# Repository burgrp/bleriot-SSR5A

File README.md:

# BleRiot SSR5A

SSR5A is a mains-powered five-channel BleRiot switch intended primarily for
zone thermo-electric actuators in hydronic heating systems. Each independently
controlled output switches mains line through a zero-cross optotriac and triac.

The board combines a PY32F030 microcontroller, PAN2110 radio, five output
channels, a WS2812B status LED, and an isolated 3.3 V mains power supply. The
outputs are on/off switches; they are not phase-angle dimmers.

## Connections

Connector numbering follows the KiCad schematic.

| Connector | Pin 1 | Pin 2 | Pin 3 |
| --- | --- | --- | --- |
| `IN1` | Line (L) | Neutral (N) | Protective earth (PE) |
| `J1` | Channel 1 switched line | Neutral | Protective earth |
| `J2` | Channel 2 switched line | Neutral | Protective earth |
| `J3` | Channel 3 switched line | Neutral | Protective earth |
| `J4` | Channel 4 switched line | Neutral | Protective earth |
| `J5` | Channel 5 switched line | Neutral | Protective earth |

Each channel uses a MOC306x zero-cross optotriac and BTA08S-600CW triac. Its
on-board indicator LED follows the output directly.

## BleRiot Registers

An enabled channel is exposed as a writable boolean register:

| Tag | Register |
| ---: | --- |
| 1 | `ssr.channel.1` |
| 2 | `ssr.channel.2` |
| 3 | `ssr.channel.3` |
| 4 | `ssr.channel.4` |
| 5 | `ssr.channel.5` |

Each channel has inventory-as-code configuration in
[`fw/cmd/dev/main.go`](fw/cmd/dev/main.go):

- `Disabled` omits the register and holds the physical output off.
- `Inverted` reverses the logical-to-physical output mapping.
- `Default` selects the logical value applied after power-on and RF link loss.

Disabled takes precedence over inversion and the default. At startup, firmware
first biases every active-low triac control inactive, then applies the configured
defaults.

The node considers the BleRiot link offline after five seconds without a valid
packet. On the online-to-offline transition, it immediately restores every
channel to its configured logical `Default` and reapplies the corresponding
physical output level. This fail-safe also honors `Inverted`; for example, an
inverted channel with `Default: false` is physically energized while offline.
Choose defaults for the required safe state of the installation.

The smart LED on `PA6` shows the link and logical channel state. While online it
uses the idle color when every enabled channel register is false and the active
color when at least one is true, regardless of output inversion. It blinks red
while the link is offline.

The RF-loss behavior has been verified on hardware: channel 1 was commanded on,
the hub was stopped, and its active-low MCU output returned inactive after the
five-second link timeout. After reconnecting, all five registers reported their
configured false defaults.

## Hardware And Firmware

| Function | MCU pin |
| --- | --- |
| Channel 1 | `PA11` |
| Channel 2 | `PA12` |
| Channel 3 | `PA15` |
| Channel 4 | `PB3` |
| Channel 5 | `PB4` |
| WS2812B data | `PA6` |
| PAN2110 CSN | `PA4` |
| PAN2110 SCK | `PA5` |
| PAN2110 data | `PA7` |

The importable `ssr5a` firmware exports `Run` and targets the `py32f030x8`
profile. Its device type owns the scheduler-none build policy and 100 kHz
attach-mode pyOCD settings. The local inventory bridges the radio node to a
Registry server. The SWD connector carries SWDIO, ground, and SWCLK but no reset
or target-voltage connection.

## Repository Layout

- [`board/`](board/) contains the KiCad schematic, PCB, BOM, and fabrication
  outputs.
- [`fw/`](fw/) contains the importable TinyGo firmware, tests, and build profile.
- [`fw/spec/`](fw/spec/) contains configuration, the config-dependent register
  table, chip, and firmware manifest.
- [`fw/cmd/dev/`](fw/cmd/dev/) contains the local inventory and BleRiot CLI.
- [`fw-orig/`](fw-orig/) contains the original MicroPython firmware for reference.
- [`sub/hw-kicad/`](sub/hw-kicad/) is the shared KiCad library submodule.

Initialize the shared hardware library after cloning:

```sh
git submodule update --init --recursive
```

## Build And Test

The firmware requires Go, TinyGo with Puya target support, GNU Arm Embedded
binutils, and pyOCD with the Puya CMSIS pack.

```sh
go -C fw test ./...
go -C fw run ./cmd/dev node gen --name ssr
go -C fw run ./cmd/dev node build --name ssr --disassembly
go -C fw run ./cmd/dev node build --name ssr --flash --rtt
```

With a Registry server running, start the local hub:

```sh
go -C fw run ./cmd/dev hub --registry http://localhost:8080 --diagnostics rf
```

## Safety

This design connects directly to hazardous mains voltage. Assembly,
installation, testing, and enclosure work must be performed by suitably
qualified people using applicable electrical codes and safe isolation
practices. Independently verify protection, creepage and clearance, protective
earth continuity, enclosure construction, triac thermal limits, and actuator
ratings before deployment.

Do not wire mains or an actuator from this README alone. Verify the assembled
board against the schematic, PCB, and actuator manufacturer's documentation.

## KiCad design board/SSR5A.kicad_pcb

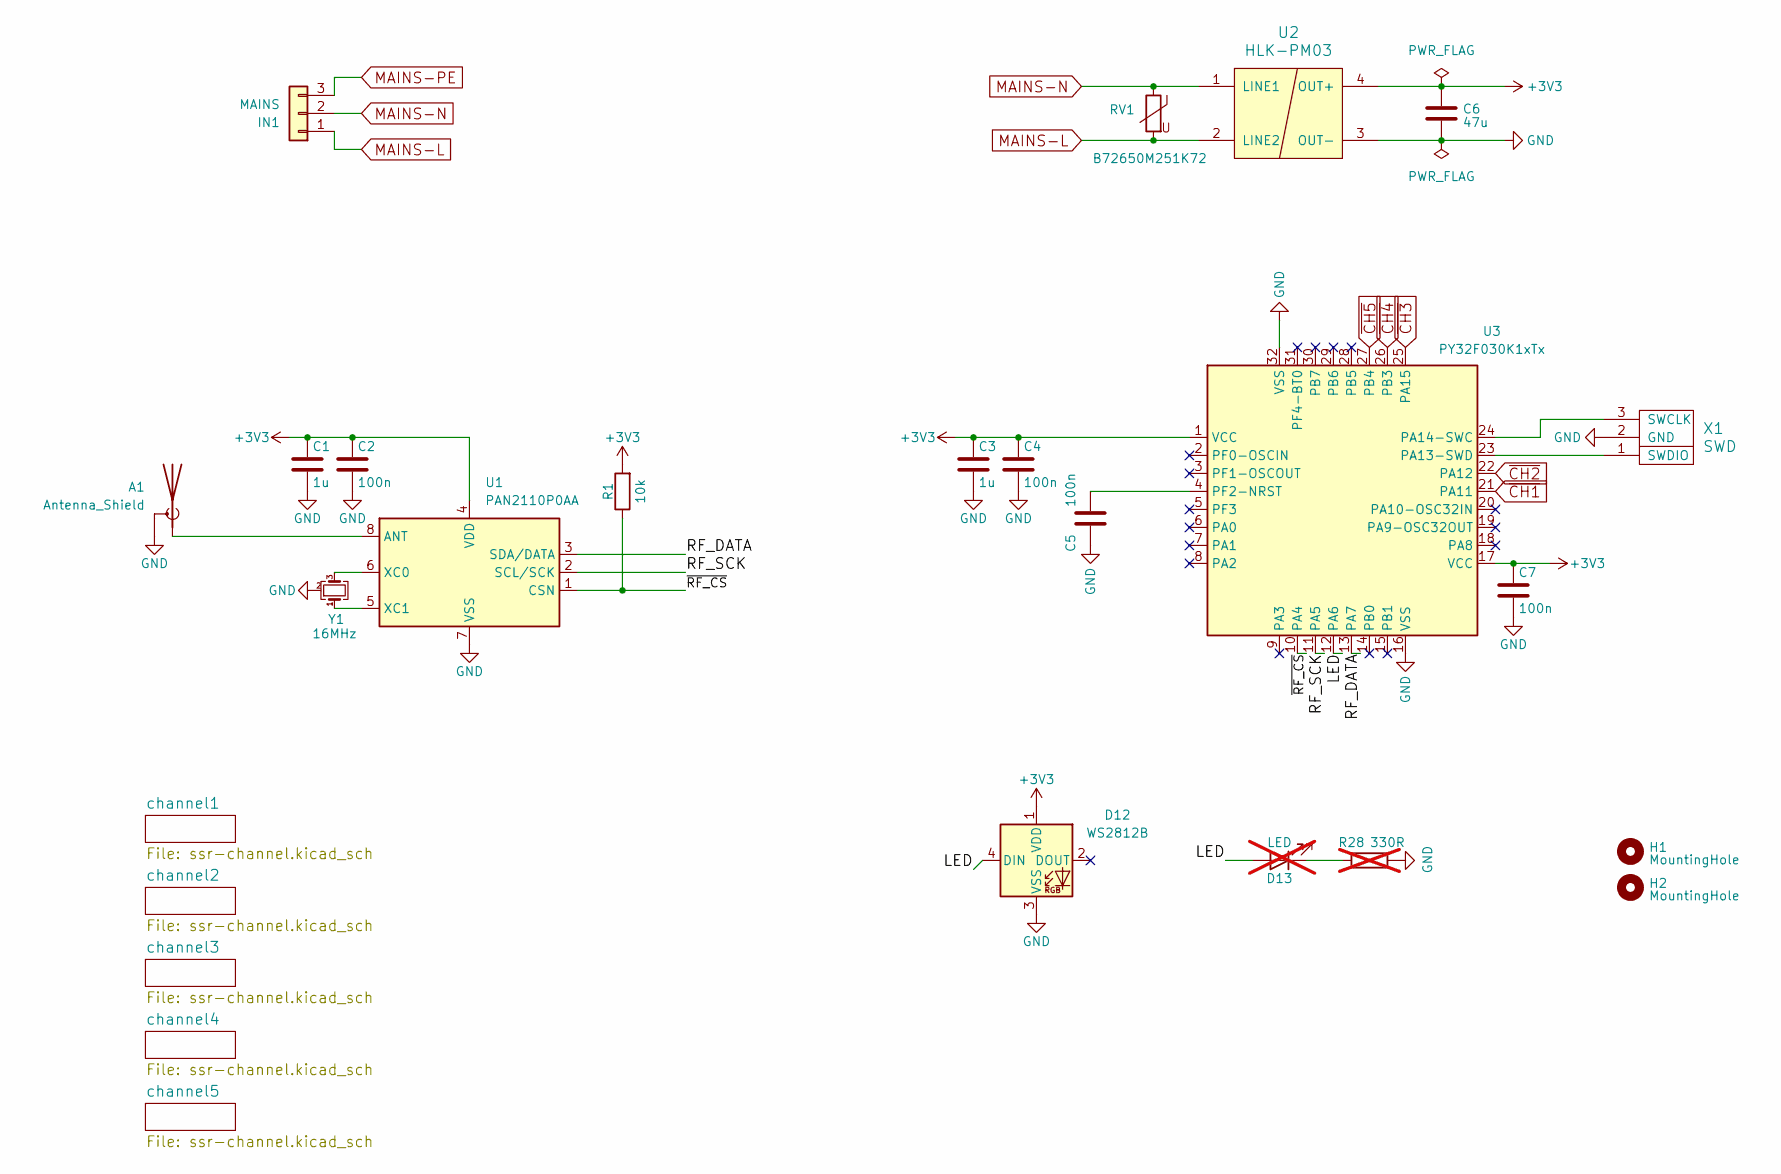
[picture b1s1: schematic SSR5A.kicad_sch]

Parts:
A1: Antenna_Shield; Texas_SWRA117D_2.4GHz_Right
C1, C3: 1u; C_0805_2012Metric
C2, C4, C5, C7: 100n; C_0805_2012Metric
C6: 47u; C_0805_2012Metric
D12: WS2812B; LED_WS2812B_PLCC4_5.0x5.0mm_P3.2mm
D13: LED; LED_0805_2012Metric_Pad1.15x1.40mm_HandSolder; not fitted
H1, H2: MountingHole; MountingHole_3.7mm_Pad_Via
IN1: MAINS; PhoenixContact_MSTBA_2,5_3-G_1x03_P5.00mm_Horizontal
R1: 10k; R_0805_2012Metric
R28: 330R; R_0805_2012Metric; not fitted
RV1: B72650M251K72; R_1210_3225Metric
U1: PAN2110P0AA; SOIC-8_3.9x4.9mm_P1.27mm
U2: HLK-PM03; HLK-PM01
U3: PY32F030K1xTx; LQFP-32_7x7mm_P0.8mm
X1: SWD
Y1: 16MHz; Crystal_SMD_3225-4Pin_3.2x2.5mm

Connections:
+3V3: C1.1, C2.1, C3.1, C4.1, C6.1, C7.1, D12.1 (VDD), R1.2, U1.4 (VDD), U2.4 (OUT+), U3.1 (VCC), U3.17 (VCC); also elsewhere on the board
/LED: D12.4 (DIN), D13.2 (A), U3.12 (PA6)
/RF_DATA: U1.3 (SDA/DATA), U3.13 (PA7)
/RF_SCK: U1.2 (SCL/SCK), U3.11 (PA5)
/~RF_CS: R1.1, U1.1 (CSN), U3.10 (PA4)
GND: A1.2 (Shield), C1.2, C2.2, C3.2, C4.2, C5.2, C6.2, C7.2, D12.3 (VSS), R28.1, U1.7 (VSS), U2.3 (OUT-), U3.16 (VSS), U3.32 (VSS), X1.2 (GND), Y1.2 (G), Y1.4 (G)
MAINS-L: IN1.1, RV1.2, U2.2 (LINE2); also elsewhere on the board
MAINS-N: IN1.2, RV1.1, U2.1 (LINE1); also elsewhere on the board
MAINS-PE: IN1.3; also elsewhere on the board
unnamed: A1.1 (A), U1.8 (ANT)
unnamed: D13.1 (K), R28.2
unnamed: U1.6 (XC0), Y1.3
unnamed: U1.5 (XC1), Y1.1
unnamed: U3.23 (PA13-SWD), X1.1 (SWDIO)
unnamed: U3.24 (PA14-SWC), X1.3 (SWCLK)
unnamed: C5.1, U3.4 (PF2-NRST)
~CH2: U3.22 (PA12); also elsewhere on the board
~CH3: U3.25 (PA15); also elsewhere on the board
~CH4: U3.26 (PB3); also elsewhere on the board
~CH5: U3.27 (PB4); also elsewhere on the board

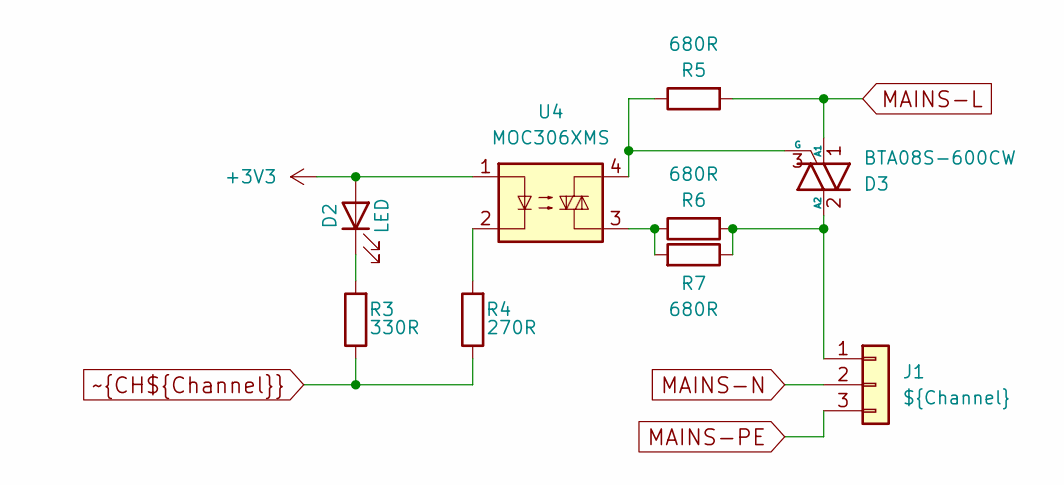
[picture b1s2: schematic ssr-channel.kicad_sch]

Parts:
D2: LED; LED_0805_2012Metric_Pad1.15x1.40mm_HandSolder
D3: BTA08S-600CW; TO-252-2
J1: ${Channel}; PhoenixContact_MSTBA_2,5_3-G_1x03_P5.00mm_Horizontal
R3: 330R; R_0805_2012Metric
R4: 270R; R_0805_2012Metric
R5, R6, R7: 680R; R_0805_2012Metric
U4: MOC306XMS; SMDIP-4_W7.62mm

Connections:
+3V3: D2.2 (A), U4.1; also elsewhere on the board
MAINS-L: D3.1 (A1), R5.2; also elsewhere on the board
MAINS-N: J1.2; also elsewhere on the board
MAINS-PE: J1.3; also elsewhere on the board
unnamed: D2.1 (K), R3.2
unnamed: D3.2 (A2), J1.1, R6.2, R7.1
unnamed: D3.3 (G), R5.1, U4.4
unnamed: R4.2, U4.2
unnamed: R6.1, R7.2, U4.3

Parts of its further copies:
D4, D6, D8, D10: LED; LED_0805_2012Metric_Pad1.15x1.40mm_HandSolder
D5, D7, D9, D11: BTA08S-600CW; TO-252-2
R8, R13, R18, R23: 330R; R_0805_2012Metric
R9, R14, R19, R24: 270R; R_0805_2012Metric
R10, R11, R12, R15, R16, R17, R20, R21, R22, R25, R26, R27: 680R; R_0805_2012Metric
U5, U6, U7, U8: MOC306XMS; SMDIP-4_W7.62mm

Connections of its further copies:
+3V3: D4.2 (A), D6.2 (A), D8.2 (A), D10.2 (A), U5.1, U6.1, U7.1, U8.1; also elsewhere on the board
MAINS-L: D5.1 (A1), D7.1 (A1), D9.1 (A1), D11.1 (A1), R10.2, R15.2, R20.2, R25.2; also elsewhere on the board
unnamed: D4.1 (K), R8.2
unnamed 14: D5.2 (A2), R11.2, R12.1; also elsewhere on the board
unnamed: D5.3 (G), R10.1, U5.4
unnamed: D6.1 (K), R13.2
unnamed 17: D7.2 (A2), R16.2, R17.1; also elsewhere on the board
unnamed: D7.3 (G), R15.1, U6.4
unnamed: D8.1 (K), R18.2
unnamed 20: D9.2 (A2), R21.2, R22.1; also elsewhere on the board
unnamed: D9.3 (G), R20.1, U7.4
unnamed: D10.1 (K), R23.2
unnamed 23: D11.2 (A2), R26.2, R27.1; also elsewhere on the board
unnamed: D11.3 (G), R25.1, U8.4
unnamed: R9.2, U5.2
unnamed: R11.1, R12.2, U5.3
unnamed: R14.2, U6.2
unnamed: R16.1, R17.2, U6.3
unnamed: R19.2, U7.2
unnamed: R21.1, R22.2, U7.3
unnamed: R24.2, U8.2
unnamed: R26.1, R27.2, U8.3
~CH2: R8.1, R9.1; also elsewhere on the board
~CH3: R13.1, R14.1; also elsewhere on the board
~CH4: R18.1, R19.1; also elsewhere on the board
~CH5: R23.1, R24.1; also elsewhere on the board

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
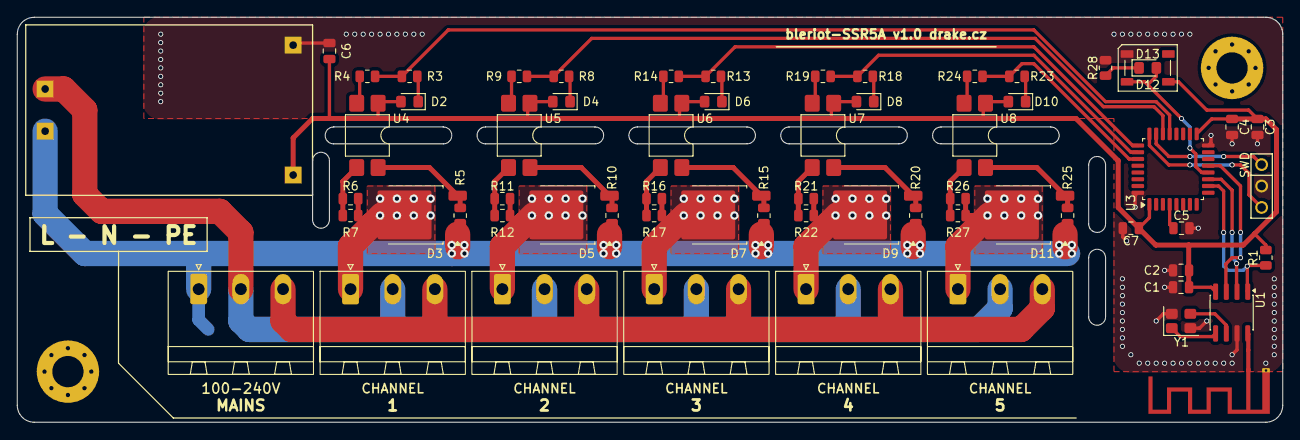
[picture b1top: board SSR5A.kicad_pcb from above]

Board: 2 copper layers, 150.0 x 48.0 mm, 66 parts (1 on the bottom side), 46 nets.

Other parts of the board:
J2: 2; PhoenixContact_MSTBA_2,5_3-G_1x03_P5.00mm_Horizontal
J3: 3; PhoenixContact_MSTBA_2,5_3-G_1x03_P5.00mm_Horizontal
J4: 4; PhoenixContact_MSTBA_2,5_3-G_1x03_P5.00mm_Horizontal
J5: 5; PhoenixContact_MSTBA_2,5_3-G_1x03_P5.00mm_Horizontal

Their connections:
MAINS-N: J2.2, J3.2, J4.2, J5.2; also elsewhere on the board
MAINS-PE: J2.3, J3.3, J4.3, J5.3; also elsewhere on the board
unnamed 14: J2.1; also elsewhere on the board
unnamed 17: J3.1; also elsewhere on the board
unnamed 20: J4.1; also elsewhere on the board
unnamed 23: J5.1; also elsewhere on the board
